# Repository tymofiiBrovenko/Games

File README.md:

# Arduino Memory Game1 V1

A memory game built with Arduino. The board shows you a sequence of flashing lights - your job is to repeat it by pressing the matching buttons. Every round the sequence gets one step longer. Miss a button and the game starts over.

---

## How to Play

1. Watch the LEDs flash in a sequence.
2. Press the buttons in the same order.
3. Each round adds one more step.
4. Wrong button? The buzzer sounds and all LEDs flash - game resets.

---

## Wiring

## Real Life

---

## Parts List

| Part | Qty |
|---|---|
| Arduino UNO | 1 |
| LED | 4 |
| Resistor 220 Ω | 4 |
| Push button | 4 |
| Buzzer | 1 |
| Breadboard | 1 |

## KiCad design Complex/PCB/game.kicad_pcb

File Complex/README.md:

# ESP32 + LED Matrix Snake

A classic Snake game built with an ESP32. The game is displayed on an 8x8 LED matrix and controlled with a matrix keypad. The code is structured to update the display continuously in the background, keeping the gameplay and screen rendering smooth.

## How to Play

1. Use the keypad to move the snake (Up, Down, Left, Right).
2. Eat the glowing dot to grow longer.
3. Do not hit the walls or your own tail.
4. If you crash, all LEDs will light up. Press any button to restart the game.

## Real Life

## Wiring

* **Shift Register:** DATA to pin 14, LATCH to pin 13, CLOCK to pin 12.
* **Keypad Columns:** Connected to pins 34, 35, 36, 39.
* **LED Matrix:** Rows and Columns connected to the remaining ESP32 pins (see code for the exact array).

## Parts List

| Part | Amount |
| :--- | :--- |
| ESP32 Development Board | 1 |
| 8x8 LED Matrix | 1 |
| 4x4 Keypad | 1 |
| 74HC595 Shift Register | 1 |
| Resistor 220 Ω | 8 |
| Resistor 10k Ω | 4 |
| Breadboard | 1 |

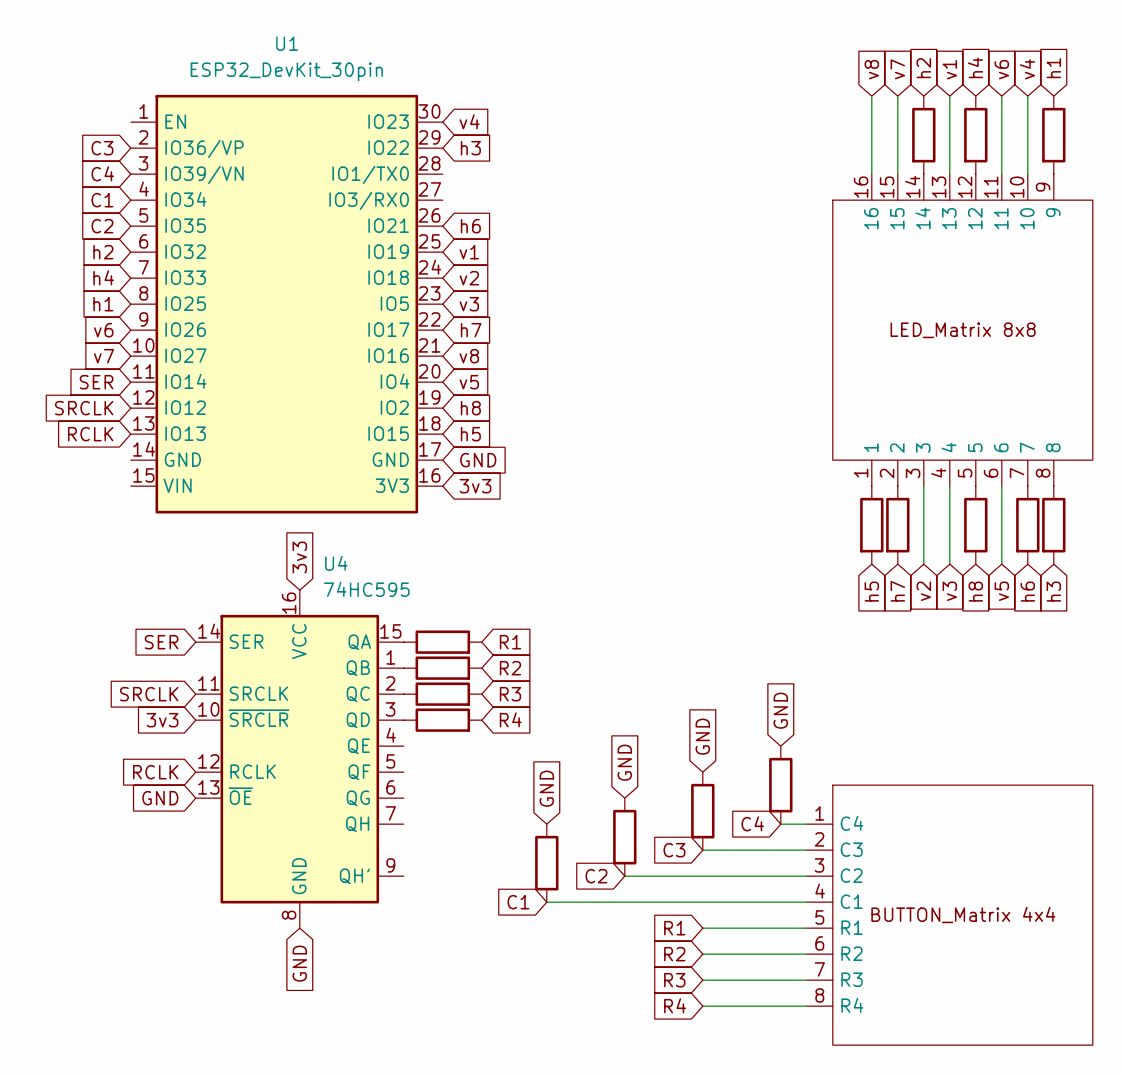
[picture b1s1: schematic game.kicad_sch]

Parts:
R1, R10, R11, R12: 10k; R_Axial_DIN0207_L6.3mm_D2.5mm_P7.62mm_Horizontal
R2, R3, R4, R5, R6, R7, R8, R9, R13, R14, R15, R16: 220; R_Axial_DIN0207_L6.3mm_D2.5mm_P7.62mm_Horizontal
U1: ESP32_DevKit_30pin; ESP32_DevKit_30pin_W25.4mm
U2: LED_Matrix_8x8_32mm_W24mm
U3: PinHeader_1x08_P2.54mm_Vertical
U4: 74HC595; DIP-16_W7.62mm

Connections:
3v3: U1.16 (3V3), U4.10 (~SRCLR), U4.16 (VCC)
GND: R1.1, R10.1, R11.1, R12.1, U1.17 (GND), U4.8 (GND), U4.13 (~OE)
unnamed: R2.1, U2.1
unnamed: R3.1, U2.2
unnamed: R4.1, U2.5
unnamed: R5.1, U2.7
unnamed: R6.1, U2.8
unnamed: R7.2, U2.9
unnamed: R8.2, U2.12
unnamed: R9.2, U2.14
unnamed: R13.1, U4.15 (QA)
unnamed: R14.1, U4.1 (QB)
unnamed: R15.1, U4.2 (QC)
unnamed: R16.1, U4.3 (QD)
R1: R13.2, U3.5 (R1)
R2: R14.2, U3.6 (R2)
R3: R15.2, U3.7 (R3)
R4: R16.2, U3.8 (R4)
RCLK: U1.13 (IO13), U4.12 (RCLK)
SER: U1.11 (IO14), U4.14 (SER)
SRCLK: U1.12 (IO12), U4.11 (SRCLK)
h1: R7.1, U1.8 (IO25)
h2: R9.1, U1.6 (IO32)
h3: R6.2, U1.29 (IO22)
h4: R8.1, U1.7 (IO33)
h5: R2.2, U1.18 (IO15)
h6: R5.2, U1.26 (IO21)
h7: R3.2, U1.22 (IO17)
h8: R4.2, U1.19 (IO2)
v1: U1.25 (IO19), U2.13
v2: U1.24 (IO18), U2.3
v3: U1.23 (IO5), U2.4
v4: U1.30 (IO23), U2.10
v5: U1.20 (IO4), U2.6
v6: U1.9 (IO26), U2.11
v7: U1.10 (IO27), U2.15
v8: U1.21 (IO16), U2.16
С1: R12.2, U1.4 (IO34), U3.4 (C1)
С2: R11.2, U1.5 (IO35), U3.3 (C2)
С3: R10.2, U1.2 (IO36/VP), U3.2 (C3)
С4: R1.2, U1.3 (IO39/VN), U3.1 (C4)

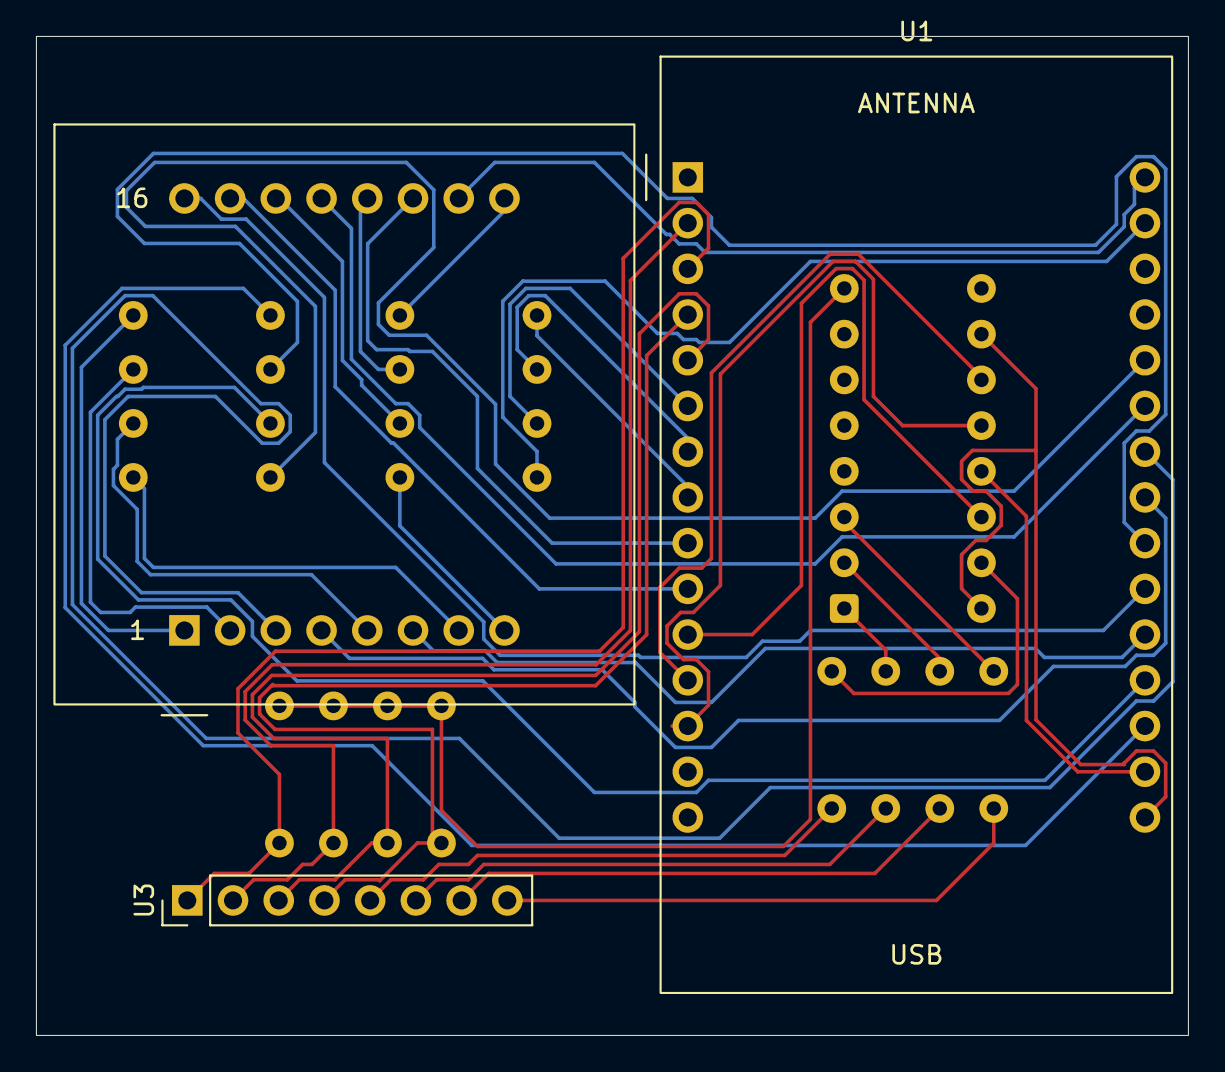
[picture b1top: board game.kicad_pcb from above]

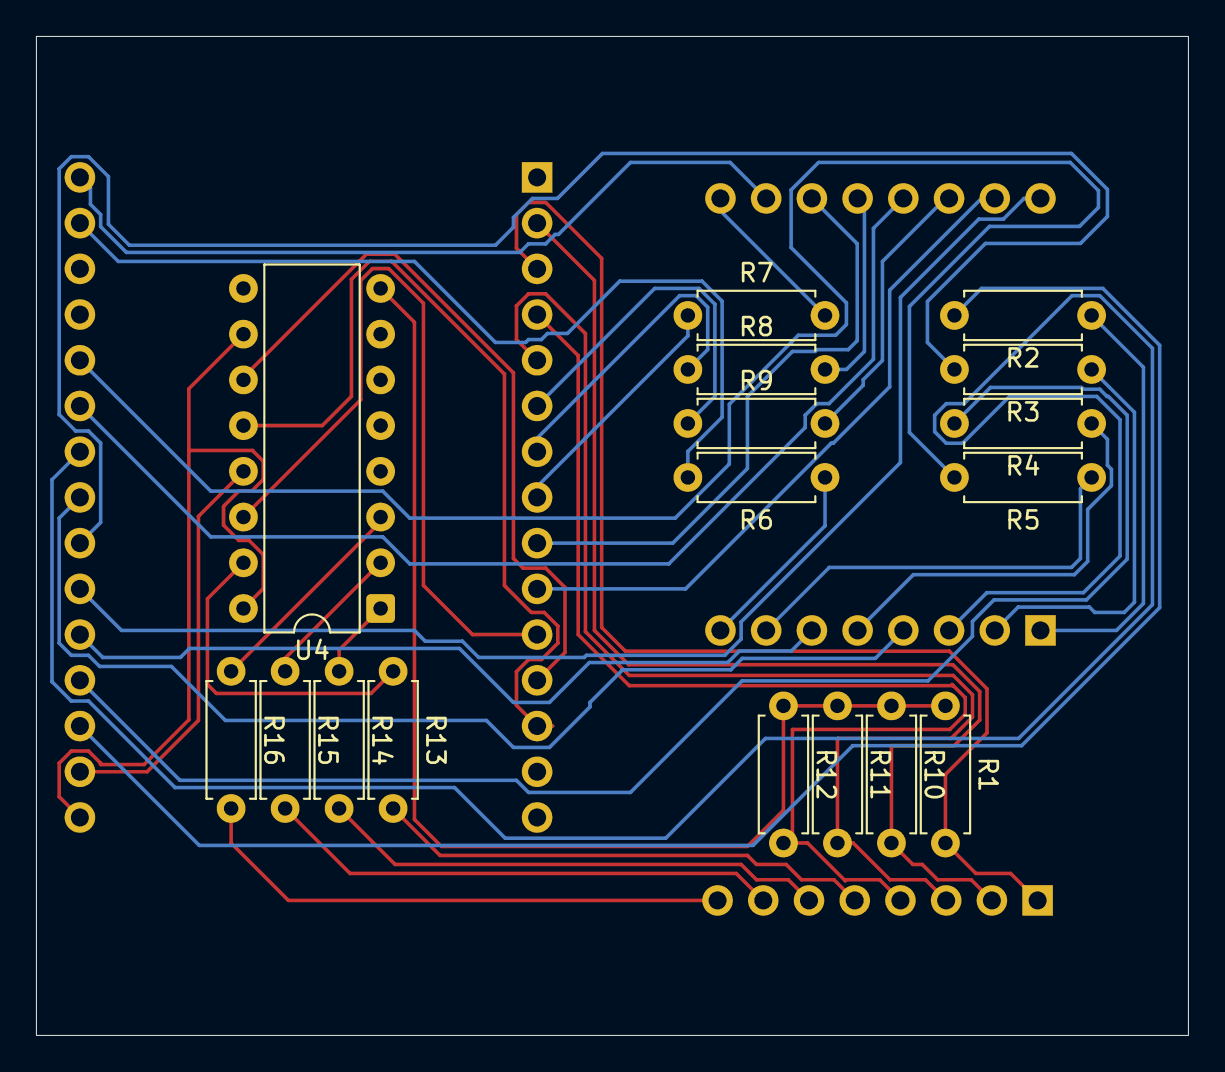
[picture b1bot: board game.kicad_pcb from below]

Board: 2 copper layers, 64.0 x 55.5 mm, 20 parts (17 on the bottom side), 41 nets.

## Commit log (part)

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2026-03-28 Revise README for Arduino Memory Game
    Updated the README to reflect the new title and added detailed instructions on how to play the Arduino memory game, along with wiring and parts list.
2026-03-28 Refactor README for clarity and conciseness
    Updated README to remove duplicate sections and improve clarity.
2026-03-28 Fix punctuation in README description and instructions
    Updated punctuation and formatting in the README.
2026-04-27 Add Real Life section with an image to README
2026-06-02 Create ö
2026-06-02 Rename README (1).md to README.md
2026-06-02 Create 1
